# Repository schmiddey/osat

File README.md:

# osat
Open Source Airsoft Target, WLAN-based Smart Target System

# Overview
The idea of the target system is, that you have one base station (Raspi Pi as WLAN AP) and many target satelites.
The Targets contain a Wemos D1 mini, a Neopixel LED, and a Piezo sensor behind a Polycarbonate plate.

More info is coming !!!

# Process
Currently only the firmware and maybe the hardware is ready or alpha state :)

The Software for the Raspi has to be done next.

note: this was my first try in hardware desigen (KiCAD) and CAD (OpenSCAD) so lets see :)

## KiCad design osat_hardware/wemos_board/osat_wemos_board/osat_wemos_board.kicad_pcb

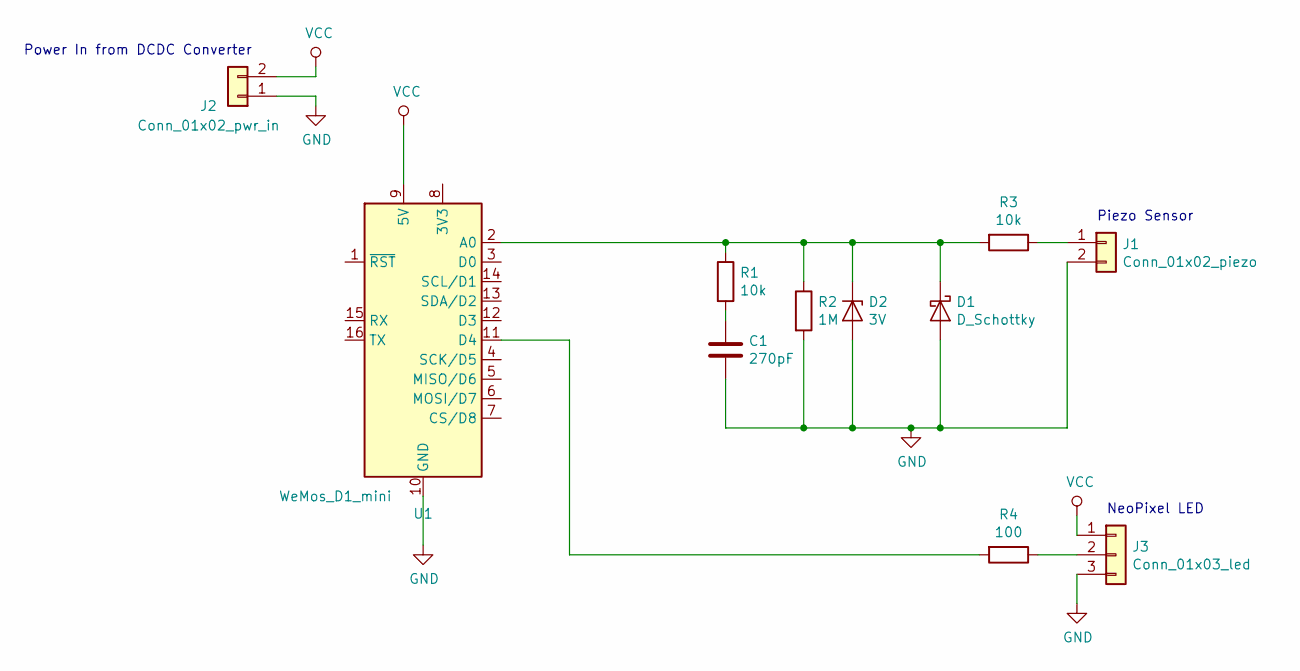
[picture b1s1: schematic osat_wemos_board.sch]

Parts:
C1: 270pF; C_Disc_D4.3mm_W1.9mm_P5.00mm
D1: D_Schottky; D_A-405_P2.54mm_Vertical_AnodeUp
D2: 3V; D_A-405_P2.54mm_Vertical_AnodeUp
J1: Conn_01x02_piezo; JST_EH_B2B-EH-A_1x02_P2.50mm_Vertical
J2: Conn_01x02_pwr_in; JST_EH_B2B-EH-A_1x02_P2.50mm_Vertical
J3: Conn_01x03_led; JST_EH_B3B-EH-A_1x03_P2.50mm_Vertical
R1, R3: 10k; R_Axial_DIN0204_L3.6mm_D1.6mm_P2.54mm_Vertical
R2: 1M; R_Axial_DIN0204_L3.6mm_D1.6mm_P2.54mm_Vertical
R4: 100; R_Axial_DIN0204_L3.6mm_D1.6mm_P2.54mm_Vertical
U1: WeMos_D1_mini; WEMOS_D1_mini_light

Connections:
GND: C1.1, D1.2 (A), D2.2 (A), J1.2, J2.1, J3.3, R2.2, U1.10 (GND)
unnamed: C1.2, R1.2
unnamed: D1.1 (K), D2.1 (K), R1.1, R2.1, R3.2, U1.2 (A0)
unnamed: J1.1, R3.1
unnamed: J3.2, R4.1
unnamed: R4.2, U1.11 (D4)
VCC: J2.2, J3.1, U1.9 (5V)

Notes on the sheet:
Piezo Sensor
NeoPixel LED
Power In from DCDC Converter

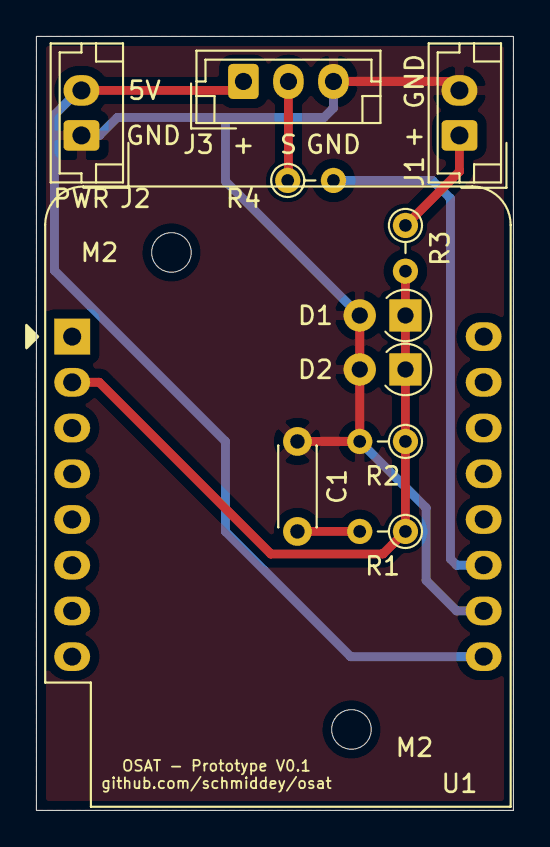
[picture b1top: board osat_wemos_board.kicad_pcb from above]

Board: 2 copper layers, 26.5 x 43.0 mm, 13 parts (0 on the bottom side), 7 nets.

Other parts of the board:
M2, M2#2: MountingHole_2.2mm_M2

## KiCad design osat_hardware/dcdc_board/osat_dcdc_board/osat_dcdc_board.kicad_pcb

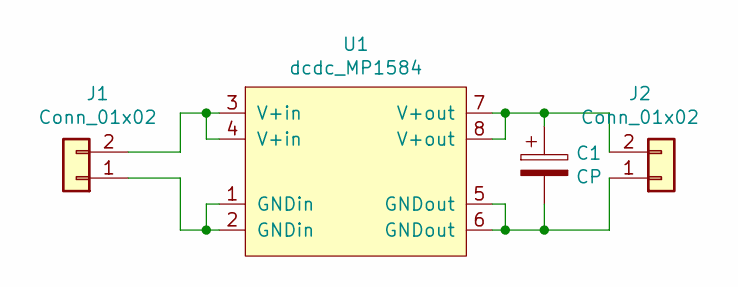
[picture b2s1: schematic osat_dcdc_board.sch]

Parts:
C1: CP; CP_Radial_D8.0mm_P5.00mm
J1, J2: Conn_01x02; JST_EH_B2B-EH-A_1x02_P2.50mm_Vertical
U1: dcdc_MP1584; MP1584EN_dcdc

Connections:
unnamed: C1.1, J2.2, U1.7 (V+out), U1.8 (V+out)
unnamed: C1.2, J2.1, U1.5 (GNDout), U1.6 (GNDout)
unnamed: J1.1, U1.1 (GNDin), U1.2 (GNDin)
unnamed: J1.2, U1.3 (V+in), U1.4 (V+in)

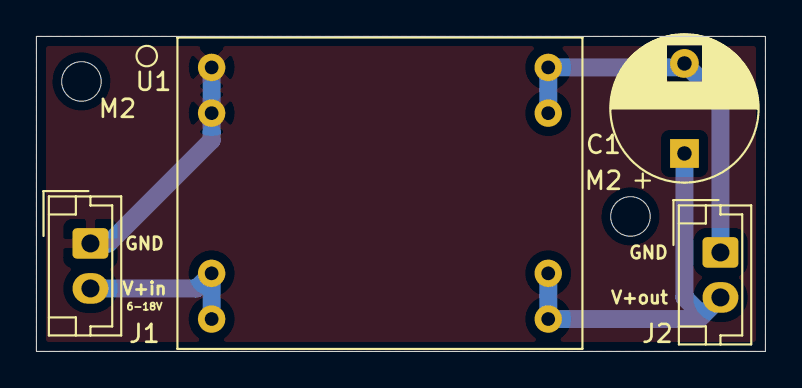
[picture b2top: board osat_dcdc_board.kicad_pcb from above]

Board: 2 copper layers, 40.5 x 17.5 mm, 6 parts (0 on the bottom side), 4 nets.

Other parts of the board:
M2, M2#2: MountingHole_2.2mm_M2

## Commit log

2020-03-01 init push
2020-03-05 updated CAD model (but hacked :D ) added mounts for pcp and added holes for wemos usb port and 5.5mm power con
2020-03-05 added sending config in idle state, and changed tcp input parser... no sends cfg if changed
2020-03-08 added new cmd on firmware for requesting config and further small changes, added also offline test firmware (only flashing)
2020-03-21 minor changes overall... first commit with osat_server and osat_clients working (3 modes)
2020-03-28 added modes working correctly, added scan for osats, alpha state of osat_server_terminal
